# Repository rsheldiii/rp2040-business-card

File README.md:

# How to make Doom run on a business card!

Maybe you're like me, you're mindlessly scrolling through social media and between all the NileRed and LegalEagle shorts you see a video about someone running Doom on their smart fridge or something. You LQTM and keep scrolling, but something's nagging at the back of your brain — why Doom? ow do people even figure this stuff out? And, can I do something like that? I'm here to tell you you can, even if - like me - you don't have a single hardware hacker bone in your body.

# What is Doom? What is "It Runs Doom"?

Let's do some quick housekeeping, just in case:

## What is Doom?

Doom is a popular 1990's shooter game - a boomer shooter, but back when boomer shooters were just called shooters, but also... did Boomers play shooters? Doom came out in 1993, boomers were like 40 years old by then. Anyways, Doom builds off the fundamentals of predecessors like Wolfenstein, featuring a first-person perspective, an arsenal of weaponry and intricate level design. Doom's code was famously open-sourced, and famously well written, which has, in part, led to the proliferation of the "It Runs Doom" meme. If you'd like to learn more about how Doom works, I highly recommend the ["Game Engine Black Book Doom"](https://fabiensanglard.net/gebbdoom/), which goes into much more detail than I would be able to.

## What is "It Runs Doom"?

"It Runs Doom" is a popular [memetic construct](https://knowyourmeme.com/memes/it-runs-doom) where by pure skill or psychotic devotion, a programmer gets Doom running on something it probably shouldn't. Maybe that's a printer, or an ipod mini, or an oscilloscope, or even... a pregnancy test? Well, yes, but also... no. but... kind of?

# What qualifies as "Running Doom"?

I'd argue there are 3 main ways to run Doom on something: 

## Compilation 

The first, and most classic, is via compilation: you upload a program to the device that uses the device's original hardware to interpret and display Doom. Depending on the device, this is easier or harder than you might think; if the device is using a common, powerful consumer chip and has an exposed UART or other debug programming header, it could be about as easy as writing a screen driver. If the device is locked down, or Doom hasn't ever been compiled for the hardware, or you hit memory or space limitations, things can spiral in complexity pretty quickly. At the end of the day though, making Doom run on original hardware breaks down into three high-level steps:

1. You need to gain write access
2. You need to compile doom for the hardware target, taking into account any hardware limitations
3. You need to adapt the display, audio, and input code to use the device's hardware

That's about as much as I'm qualified to explain due to aforementioned lack of hardware-hacking ossicles. There are thousands upon thousands of different types of consumer devices with the capability to run Doom, and probably just as many people better equipped to explain how to do so, so we'll leave this category to the side for now.

# Display

The second way to run Doom applies to things like dot matrix displays or an oscilloscope: you get Doom running on something _else_ in a way that the display device can interpret. The name of the game here is to find a device that can both play Doom and talk to the display in whatever way the display wants to be talked to, then do both at the same time. That can be very straightforward in the case of a dot matrix display, but can get _very_ complicated - like when running doom on a [stock NES](https://youtu.be/FzVN9kIUNxw). This is not a port, somebody stuck an entire raspberry pi in a NES cartridge and made it spit out code that "tricks" the NES into displaying Doom, which is absolutely insane.

# Creation

The final way to run Doom is to take the original hardware _out_ of the device and run Doom on custom-built hardware _inside_ the device, the most famous example of this being the [pregnancy test](https://www.popularmechanics.com/science/a33957256/this-programmer-figured-out-how-to-play-doom-on-a-pregnancy-test/), but I also made a [keycap](https://github.com/rsheldiii/rp2040-doom-lcd) that runs doom, and [this madlad](https://youtu.be/o76U0JPrMFk) got Doom running on a LEGO brick in much the same way. 

While this is not nearly the same as hacking Doom onto a printer while sidestepping encryption and sniffing protocols, it's not the soulless copout some people would have you believe. If you make your own device that runs Doom, you'll gain a ton of knowledge about:

* PCB design
* Crystal oscillator circuits
* The USB specification
* Miniaturization and efficient trace routing
* Early 90's programming
* And more! 

I'm going to walk you through everything I learned getting Doom to run in a couple of different form factors so that you too can make your own device that runs Doom!

# Creating a PCB that runs Doom

The best way to solve a difficult problem is to remove constraints until you can solve it, then add them back one by one. _Understanding_ a problem mirrors this construction; Using my keycap to demonstrate how to design a device that can run Doom would be confusing, as I was designing for a small form factor. Components are crushed together, vias are placed in the middle of pads, traces take 90-degree turns where they really shouldn't take 90-degree turns, the works. I don't want you picking up any more of my bad habits than absolutely necessary, so let's start with something a bit more straightforward, and a LOT bigger: My business card!

I want to stress this is not _the_ business card that runs doom, it is _a_ business card that _can_ run doom. it can also run a NES emulator and lots of other things too, and has a handy set of GPIO pins at the top. Despite the larger form factor, the circuit is fundamentally the same, just all on one side and much easier to follow.

# Prototyping

But, how did we get here? How did we go from saying "I want to run Doom on my X" to having an X that runs Doom?

Well, step 0 is to have somebody else do it first. Graham Sanderson from the Raspberry Pi foundation wrote a _fantastic_ port of Choco Doom as part of the promotional material for the RP2040. Graham jumped through an amazing amount of hoops to get Doom running on the RP2040, like optimizing WAD file size by over 50% and writing some assembler PIO code to output to VGA, which can be displayed via HDMI. I took Graham's code and built off of it by uh... very carefully ripping out some of those optimizations, and implementing some generic SPI/I2c screen support. if you'd like to learn more about the crazy stuff graham did in his port, I highly recommend his detailed rundown on his [github page](https://kilograham.github.io/rp2040-doom/).

So after step 0, step 1 is to prototype. This mess of wires:

is my original prototype, and believe it or not, it still works! Prototyping is all about the loop: 

* Get to a known good state, then
* Implement a new feature (and inevitably break the build)

then repeat. For this project, that meant flashing the firmware in the first place, then getting just the LED blinking every frame, then unwinding the DVI linebuffer code in favor of a generic SPI / I2c interface. The actual process for this step is very boring, and I've already done it for you, so we'll move on from here.

So now we've got our prototype working, Doom is playing on a Raspberry Pi Pico hooked up to an Adafruit amplifier board (more on that later) and an OLED breakout. I could have made a carrier board for all these devices, slapped my name and email on it and called it a day; that's definitely a business card, and it would definitely run Doom. But we'd be wasting a lot of the potential of the pico with it's 26 I/O pins, it'd be impossible to make small enough to fit in a keycap, and also that's pretty underwhelming.

So, If we wanted to make our own, custom board, what would it need to "run" Doom? like, what components from the ones we've already assembled are necessary for that purpose?

# Component Requirements

### Processor

For starters, you need a processor, and we've got ourselves covered with the Raspberry Pi RP2040. Featuring a dual-core Arm Cortex m0, 264KB of SRAM, and support for up to 16MB of flash... it doesn't seem like it's big enough, does it? I mean, it's way fast enough, but I'll be forever in awe of how Graham got doom running on a 16th of the original RAM requirements. We could use the new RP2350 here - in fact Doom would run even better - but I'll be damned if I can find the bare MCU anywhere...

### Crystal Oscillator

but what else do you need to run Doom? Well, the RP2040 _needs_ a crystal oscillator... sort of. Every microcontroller needs at least one oscillator to run the clock, but the RP2040 already has an oscillator, it just kind of sucks. it's there for boot initialization, but it's accuracy is terrible, literally between 1.8 and 12MHZ. You can physically run the RP2040 without an external crystal, and the rp2040 might crunch the numbers that could theoretically put Doom on a screen, but you'd have to clock an i2c screen way, _way_ down to get anything to show - we're talking a couple FPS at most. So in any case, in our circumstance, we absolutely need an external crystal oscillator.

### Flash

You also need a flash chip, so you can store Doom. Think of flash as the hard drive of the microcontroller. When compiled for the rp2040, the game code itself is only about half a megabyte, but remember how I said Doom was open-source? well, Doom the _engine_ is open source, but doom the _game_ is not, and clocks in at around 11 megabytes. Graham's compression algorithm cuts that in more than half if you remember, so you're fine with 8 megs of flash. The rp2040 is kind of particular about flash chips? we'll get to that later.

### Power

You'll need power as well, obviously. If you're not worried about efficiency, power can be pretty simple; we're going to use an LDO, or low drop-out voltage regulator, to get the RP2040 the 3.3 volts it needs from the USB lines. You could use a buck converter for higher efficiency but they usually require more support components, so we'll stick with the LDO for now.

### Is that it?

Now, some very select people might argue that you could stop here. You power the system, the microcontroller uses the crystal to communicate at high speeds with the flash chip, pulling the information it needs to run Doom - it just... doesn't display it anywhere. A younger me would argue this is sufficient - if I unplug my monitor, does my computer stop running? When I unplug the screen from my business card, each flash of the LED is another frame rendered into the ether. Is it not "running" Doom? 

But that's not really what we mean when something "plays" doom. Video games are multi-sensory, interactive experiences, if you can't _play_ a game, is it really a game at all? To that end, we need three more things: we need a screen, we need some way to input commands, and we need audio.

### Screen

Now, there are _hundreds_ of ways to add a screen to a raspberry pi. The proliferation of smart devices has ensured that aliexpress and its ilk are absolutely ensconced in a crusty layer of mini TFT and OLED screens. I found a couple SPI screens that use the same ribbon cable, meaning I can run either of them with a single footprint, but if you're willing to implement a screen driver you can use whatever you want - provided you can drive it fast enough. Whatever screen you get, make sure there's at least a good data sheet on the screen controller, or even better, a screen driver already implemented somewhere.

### Audio

For audio, I'm using an i2s amplifier. Why i2s you ask? That's uh... that's what Graham was using. The amp I'm using is in the same family as the Max98357 audio amplifier. Why _that_ audio amplifier you ask? Adafruit had a nice circuit diagram for it! In all seriousness though, the audio was already implemented, and there's a very popular, very standard amplifier that works great, so why change things? Just take the win.

### Input

Speaking of wins, for input I'm sticking with the USB input that's already implemented. You could certainly add a set of buttons that trigger of GPIO pins with some interrupts that set a bitmask that you key in to blah blah blah. Or, you could just use the USB communication that's _already implemented_, and let people use a nice, full-size keyboard for control input - or a trackball, like [this guy did](https://github.com/arkadijs/rp2040-doom/tree/rp2040-mipi)

# How was I supposed to know all that?

So that covers all the components needed to run Doom, but you might be asking, how was I supposed to know I needed all these things in the first place? Like, a 12mhz crystal oscillator? what? 

Let me introduce you, my friends, to the [RP2040 datasheet](https://datasheets.raspberrypi.com/rp2040/rp2040-datasheet.pdf). Calling it a datasheet is a bit of a misnomer: this thing is a tome. I'm pretty sure if you read this thing front to back you become a technomancer. The rp2040 datasheet is chock full of fantastic information about how the RP2040 runs and how to interact with the chip once you've got it up and running. It's where I learned about the internal oscillator, the UART debug mode, and very importantly, the [_minimal design example_](https://datasheets.raspberrypi.com/rp2040/Minimal-KiCAD.zip):

The _minimal design example_ is a reference implementation of an RP2040-based microcontroller. It's not the best microcontroller out there - it doesn't even have a status LED - but it's the bare minimum components required to get the RP2040 running stably. 

If you take a look at the pcb, you'll notice the crystal oscillator circuit looks fairly similar to the circuit on my board as well - that's because I just straight up copy-pasted it into my design before modifying it slightly. That might feel like a cop-out, but hardware manufactures, really, _really_ want you to use reference designs. They spend significant amounts of time and effort designing their chips and testing the physical and electrical properties of their devices, they'd _really_ prefer you just stick to the reference designs so the chip works just as it should. Fun little side note, the Raspberry Pi foundation actually [got burnt](https://arstechnica.com/gadgets/2019/07/raspberry-pi-4-uses-incorrect-usb-c-design-wont-work-with-some-chargers/) by not following reference designs in the past with one of their USB-C chargers, so even large companies are fallible to design mistakes.

# Introducing Kicad

OK, so we've got a reference design to base our PCB off of and the list of parts we're going to use, but how do we actually _use_ the reference design to design our PCB? Well, the reference design is a Kicad project, which happens to be a free PCB design software! Learning how to use kicad is it's own topic, and I'm not very qualified to teach it, but I learned by watching the "Getting To Blinky" series by [Contextual Electronics](https://www.youtube.com/watch?v=BVhWh3AsXQs&list=PLy2022BX6EspFAKBCgRuEuzapuz_4aJCn). Those tutorials have not been updated since Kicad 5, but there really hasn't been that much groundbreaking stuff between 5 and 7, so they're still a good watch. 

A nice thing about Kicad is the circuit and schematic designs are separate - you can lay out a circuit that performs a particular function, then link circuit symbols to schematic footprints. Once you switch to the PCB editor, those schematic footprints are linked together with what's called the "rat's nest", which correctly link together the pins of the components you laid out in the circuit diagram. neat!

Now that we have our EDA and a couple reference designs to base our components off of, we'll use the designs and the datasheets for the components to create a circuit for our custom board.

# The Circuit

While we're here, let's quickly go over some parts of the schematic that might be confusing. I'm **absolutely** not an electrical engineer, I just cosplay as one on the weekends, so take my advice with a grain of salt, but hey, the thing works so...

## Power

Up in the top you'll see the power circuitry. This stuff is dead simple and mostly borrowed from the reference schematic. One thing to call out here are the resistors - these are required for the USB-C spec, and you need _both_ of them so the plug can orient itself. Could you use one resistor and have the device still work? Probably, but I'm not in the business of probablies, go talk to the horseshoe company or whatever.

## Crystal Oscillator

Down below power delivery is the crystal oscillator. My advice is to use the reference crystal and just _never touch this part of the circuit again_. Crystal oscillators are effectively black magic, they are crazy susceptible to noise and other issues, if you get it working just leave it alone. It's actually so common to have a crystal that needs extra time to stabilize that there's a build variable - PICO_XOSC_STARTUP_DELAY_MULTIPLIER - that does so. If the reference crystal is out of stock try to find the most comparable crystal, follow the datasheet's recommendations for resistance and capacitance, stitch a healthy ground plane away from high-speed signals, enable the build variable and cross your fingers.

## Flash

After the crystal is the flash circuitry, which is ripped right out of the reference schematic. I would highly recommend staying within the same family of Winbond flash chips when you design your circuit, as the rp2040 is a bit picky about what chips it will talk with; I know the people over at [Digi-key's youtube channel](https://youtu.be/kcwvuwetgEQ?t=2979) had some trouble in this department, though that is still an excellent video to watch if you want a more general look at hardware development for the RP2040. 

## Audio

Looping around, we have the amplifier circuitry. This is very similar to Adafruit's Max98357 schematic. All resistor values were determined by looking at the data sheet to give us 9db of gain and a 50/50 mono output. It's worth noting that the Max98357 is a speaker amplifier, not a headphone amplifier; it might work with some really dinky headphones, but if you wanted a headphone-based system, you should be looking at a headphone amplifier instead.

## Screen

Making our way up here, we finally get to the screen. Schematically there isn't much to talk about here - like most small screens, the screens I'm using have their own drive circuitry, so we're really just connecting pins to bare pins here. Swapping to a new screen would require reviewing the screen's datasheet and rejiggering the connections here. The RP2040 is pretty unique in that the I2c and SPI pins can be one of many sets of pins across the board, so you can be pretty flexible with where you place the screen when designing the PCB.

## USB

Down at the bottom, we find ourselves at the USB hookup. The 27 ohm resistors (not shown) are required by the USB spec, the 56k resistors are the opposite of the resistors on the power usb - they indicate to the devices connected to the bus that we are an upstream-facing-port, and peripherals can expect power from us, since we need to power the keyboard. 

## Decoupling caps

Finally to round us off here, we find all these capacitors up at the top. These are decoupling capacitors, which are capacitors placed next to integrated circuits to absorb weird voltage spikes and dips, decoupling them from other stuff that's going on in the board. these decoupling caps are to be placed next to _every_ 3v3 pin on the rp2040. Lastly we have this LED hooked up to GPIO25 as a status LED, which is _very_ helpful if you can't get a debug session working.

# The PCB

So now we've got the entire schematic laid out, and all we have to do is turn that into a PCB! In Kicad this happens in a two-step process: first, you agonizingly collect all the footprints for your selected components, scrutinizing and painstakingly fixing any mistakes made by the conversion program that spit them out, and then you lay them all out in PCBNew and connect everything up! When I say agonizingly, I do mean _agonizingly_; I have not figured out a good way to do this. There are dozens of sites that claim to be a one-stop shop for all your eda footprint needs, but every one I've tried suffers from some sort of problem. Whether it's something mundane like terrible inventory, to something more systemic like whatever the heck Mouser's got going on, they all have their faults. For now I've settled on UltraLibrarian, which has a good set of footprints, and sometimes even 3d models, but the pins don't always make sense.

Once you have all your footprints downloaded, imported, and associated, you can start designing your PCB:

The blue lines are the "rat's nest" we talked about earlier. Your job is to eliminate all of these blue lines while following common PCB design rules and the constraints put on you by the fab. Then you run the design rules checker and do whatever it says - within reason. It's almost a game really, and real EEs are _much_ better at it than I am. But, this is what I came up with:

Power is in the top left, with audio at the bottom left, input at the bottom, flash at the bottom right, the screen top right, and finally the crystal oscillator (and GPIO) at the top. You can see that the USB lines are straight and impedance matched, we've got a nice, stitched ground plane under the crystal oscillator and the trace runs for most components are pretty short. I can already see one sin I committed, I put the 27ohm resistors for the USB lines at the USB connector, when they should be closer to the RP2040. However, "Closer" is a relative term, and we're super over-engineering this dinky lil USB bus here, so we'll be perfectly fine. That goes for the impedance and length matching as well.

# Fabrication

Now we've got a PCB that runs Doom in theory, but how do we get a PCB that runs doom... in practice?

well, you send your design to a fab! Each fab has their own rules and constraints listed on their website, sometimes with step-by-step tutorials on how to configure your EDA for their service; it's a good idea to run through these and make sure your board complies. Shoutouts to [OSHPark](https://www.oshpark.com) here who are a pretty phenomenal, US-based fab. I use them for prototyping as they don't have a minimum price. Plus, you can upload your Kicad project directly to them instead of having to generate gerber files! You have to buy stencils on a separate website but they are reasonably priced and even have a neat lil' import button. You're gonna _need_ stencils by the way, unless you can hand-solder a QFN56.

# Assembly

Once you've got your boards back from the fab, it's time for assembly. Since we built our boards around an rp2040, that means we basically have to do reflow soldering, which involves using a stencil to spread solder paste onto a pcb, placing components on the solder blobs and then "reflowing" that solder to stick the parts on the board. 

There are some tricks you can do to make this easier. Remember when I said my business card has all the components on the same side? That means I can use this little hot plate:

 to reflow 100% of the components with a single stencil. You can also use as many hand-solderable components as you can get your hands on, keeping all the non-hand-solderable components on the same side of the board. This again lets you only reflow with a single stencil, just with a little extra soldering afterwards.

I gotta be honest, even with these tricks I'm not great at this. It's best to get the solder all in one smooth motion but I always need to come back and do another go-round. Luckily you can still do some manual fixup if your solder job is uh... less than ideal.

Counter-intuitively, I find that power is everything when you're doing fixup drag-soldering like this. The more amps your soldering iron can push out, the better. My Hakko FX888D is a little beefier than my Pinecil and that makes all the difference in how easy it is to fix solder bridges. Also be sure to select a tip that can actually get into the space between the PCB and the component!

# Flashing / Programming

OK, you're now the proud owner of a custom-built PCB. Nobody else in the _world_ has a device like this in their hands, which can be kind of daunting. Like, forget Doom, how do I even get _any_ program on this device?

Luckily that's pretty easy, you boot the sucker up and press the boot button and wham bam thank you mam, bob's your uncle bessie's your aunt, you've got a USB mass storage device you can _copy_ your program onto! I cannot tell you how much of a mind-blown moment I had the first time I plugged in a Raspberry Pi Pico and saw this. This USB firmware is _embedded into the board_, it's basically impossible to brick. It's amazing. I'm so sick of programming headers and weird little boot rituals and all that junk, I want every microcontroller to use this bootloader.

The first program you should chuck on your PCB is the led blink example from the rp2040 datasheet, but that's boring, so we're going to head on over to the rp2040-doom-lcd github page and download us some Doom firmware. If you don't have your own PCB that's ok, there are a couple off-the-shelf boards that are supported as well, like the [Lilygo TT-Go T-display](https://www.aliexpress.us/item/3256803094729227.html), or these tiny little unnamed [0.42 inch RP2040 boards](https://www.aliexpress.us/item/3256805864747243.html). If you find another board that uses one of the [supported screens](https://github.com/rsheldiii/rp2040-doom-LCD/tree/rp2040/src/pico/pico-screens/screens), it should be relatively simple to get it up and running as well.

So you download your uf2 file, put your PCB into boot mode, chuck that sucker in the folder aaaand... nothing? well, _almost_ nothing. you should see the LED flash just a tiny bit when you plug things in, which probably indicates that you forgot to place the level code in memory. For testing purposes you can download the shareware version of doom free of charge. to grab the full game file, the easiest way is to pay for it on Steam; the 1-800 number the shareware file gives you is out of order, unfortunately. Once you've followed the instructions about how to shrink and load the level file into memory using picotool, _now_ you're ready for the moment of truth. 

And that's it, you got Doom playing on a custom PCB! It can be a little finnicky with what keyboards it'll allow to be connected to it, but once you do you have full control over the game. My spi / i2c code does not use DMA, but I haven't found any framerate issues; if you're implementing a larger display and having some trouble, that would be a good place to start. 

# What's next?

So where do we go from here? Well, a million different places, honestly. You could add a bluetooth chip and play with a game controller, or make the first electric gloves that run Doom, make a GPIO add-on for the flipper zero, or any number of different things. You'll need a PCB to use / modify though; unless you were following along, that's probably not in your possession right now. I don't want you to start from scratch, but I also don't want to just give out the files for my business card since it would be trivial to delete my name and slap someone elses in there. I'll do you one better by releasing this board:

I'm calling it the Doom Stamp. It's got:

* The same circuit as my business card in a very compact form factor (Status LED, separate power / data USB, boot button, optional power diodes, etc etc)
* 2-layer, 1-sided board for easy fabrication
* M2 mounting holes 
* A nice screw terminal for connecting external speakers

The Kicad files are available in [this repository](https://github.com/rsheldiii/rp2040-business-card) in the DoomStamp directory. Note that while the schematic is functionally identical and all components (save the speaker) remain the same, this exact pcb has *NOT BEEN TESTED* yet; I have boards on the way.

If you just want to play around with a tiny board built to run Doom, feel free to send the Kicad pcb file off to OSHPark (3 boards are ~$10) or generate your own gerbers. If you want to use my design as a starting point for your own creation, by all means!

# BOM shenanigans

You can generate the BOM in the schematic editor; there are also pre-generated BOMs at the base of the Kicad project. A few things to note:

### Crystal

The crystal is **NOT** the reference crystal, as they were out of stock when I made the original circuit. The crystal I used is [this one](https://www.mouser.com/ProductDetail/774-403C35E12M00000), though case-compatible 12mhz crystals will work in the circuit as long as you tweak the support capacitors.

### MCU

It's weirdly difficult to find RP2040 MCUs on Mouser, but they are [here](https://www.mouser.com/ProductDetail/358-SC091413)

### Flash

use the flash specified in the RP2040 datasheet

### Audio

find whichever Max9835x is in stock and double check via the datasheet that it's a drop-in replacement for the Max98357.

For the speaker terminal, the BOM csv has the part number (I haven't purchased it yet, so I don't have the link). You could also elect not to fill this component, and directly solder speaker wires, either way.

### Voltage Regulator

the voltage regulator I used was [this one](https://www.mouser.com/ProductDetail/onsemi/NCV1117ST33T3G?qs=8sOby8ZxZLHgqg5CFzeqiA%3D%3D), but I'd certainly look for comparable LDOs that are cheaper

### Screen / Screen FPC

the screen FPC I used is [this one](https://www.mouser.com/ProductDetail/TE-Connectivity/2328702-8?qs=w/v1CP2dgqphyFkupQxKkA%3D%3D). This FPC interfaces with two SPI displays that I know about. I purchased them from [this link](https://www.aliexpress.us/item/3256803794221438.html?gatewayAdapt=glo2usa), the 0.96 and the 1.14 inch version (the 1.14 being showcased in this document, as it is bigger and has much better colors). There may be other screens that work, though the code will need to be modified. 

### Boot Switch

the component photo is of a white switch, but the boot switch is [this one](https://www.mouser.com/ProductDetail/611-PTS636SL50SMTRLF)

### USBs

the two USB components used are [here](https://www.mouser.com/ProductDetail/640-USB4135-GF-A) and [here](https://www.mouser.com/ProductDetail/640-USB4105-GF-A-060)

### USB Diodes

the USB diodes are DNF; they would theoretically provide protection for the USB circuit and enforce power direction, but they're a little difficult to come by at the power I chose for the LDO. You'll need to bridge these pads, either with a wire, a 0-ohm resistor that's compatible with the footprint, or just solder. You could also use a regulator with less capacity and thus easier-to-find supporting diodes. Note that with the diodes installed, you need to provide separate power when programming the device, as the bottom usb will only be used for communication. 

# Does it _really_ play Doom though?

Indeed, so far throughout this document, I haven't provided any proof that the business card actually works. For posterity, I play the first level of Doom on the business card [here](https://youtu.be/YhjtOR5cU4k). Is that enough proof? what if I'm beaming a video of Doom via the USB port? I guess that means to _really_ prove it, you'll have to assemble a Doom Stamp and try it out for yourself.

# That's it

That's all, thanks for reading!

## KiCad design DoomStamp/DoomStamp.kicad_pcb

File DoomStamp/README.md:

The Doom Stamp was based off the RP2040 [Minimal Design Example](https://datasheets.raspberrypi.com/rp2040/Minimal-KiCAD.zip), and is designed as a platform to make embedded devices that run Doom (or indeed, embedded devices with i2s audio and SPI displays).

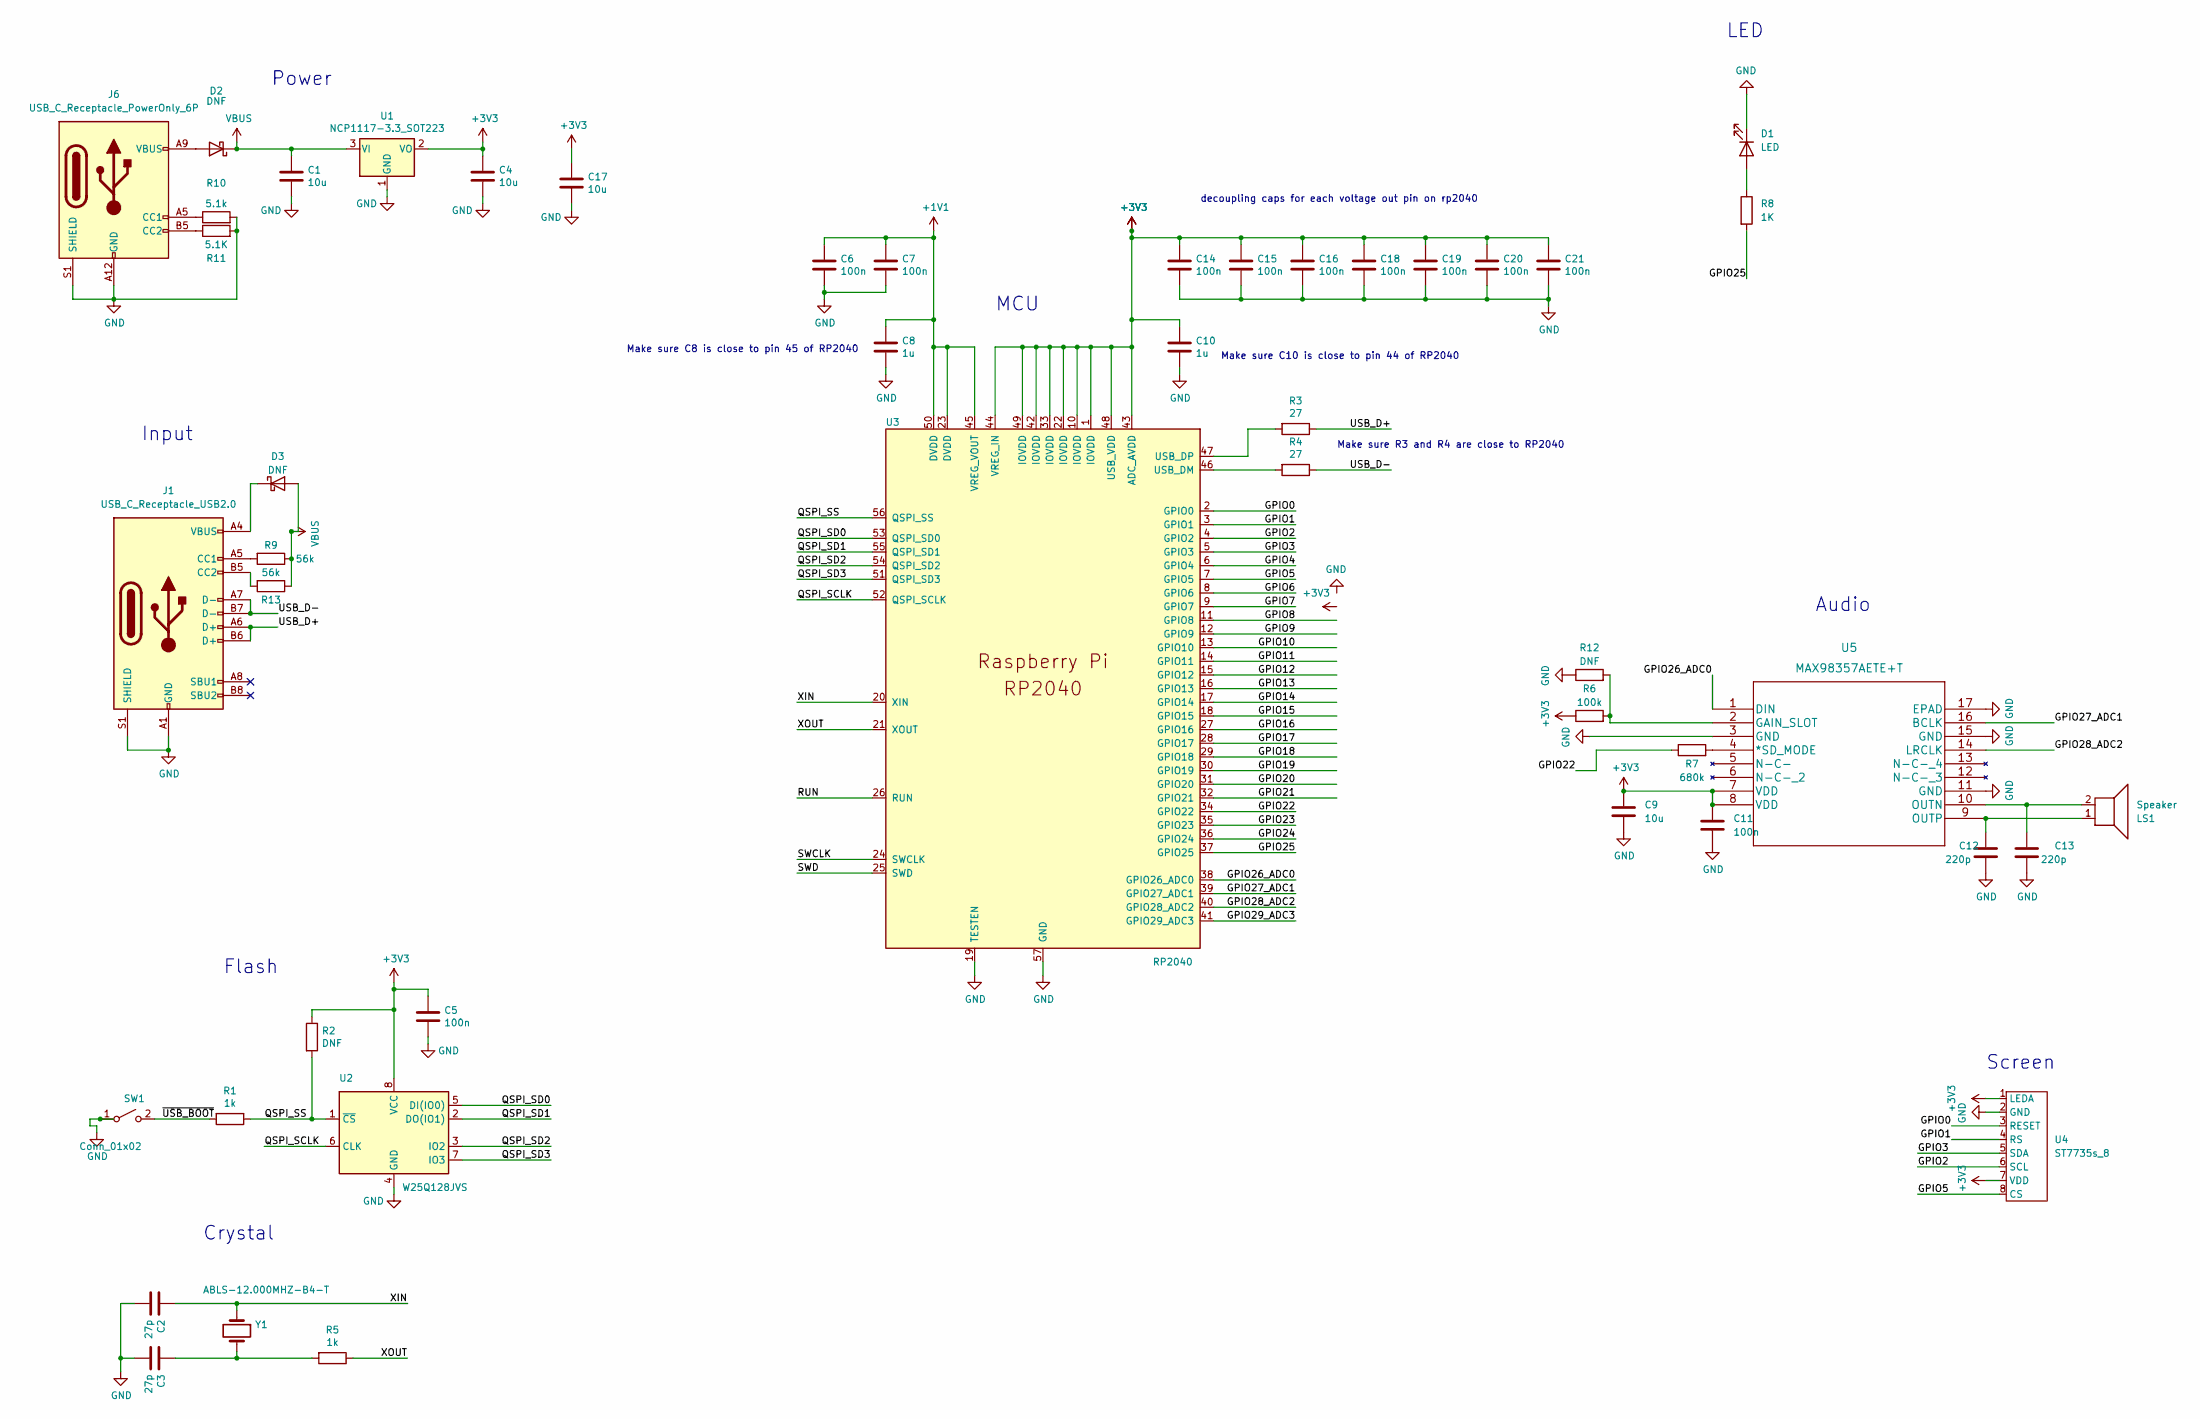
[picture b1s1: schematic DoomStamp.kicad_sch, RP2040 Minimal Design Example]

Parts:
C1, C4, C9, C17: 10u; C_0402_1005Metric
C2, C3: 27p; C_0402_1005Metric
C5, C6, C7, C11, C14, C15, C16, C18, C19, C20, C21: 100n; C_0402_1005Metric
C8, C10: 1u; C_0402_1005Metric
C12, C13: 220p; C_0402_1005Metric
D1: LED; LED_0603_1608Metric
D2, D3: DNF; D_0805_2012Metric
J1: USB_C_Receptacle_USB2.0; GCT_USB4105-GF-A
J6: USB_C_Receptacle_PowerOnly_6P; USB_C_Receptacle_GCT_USB4135-GF-A_6P_TopMnt_Horizontal
LS1: Speaker; TerminalBlock_Phoenix_MPT-0,5-2-2.54_1x02_P2.54mm_Horizontal
R1, R5: 1k; R_0402_1005Metric
R2, R12: DNF; R_0402_1005Metric
R3, R4: 27; R_0402_1005Metric
R6: 100k; R_0402_1005Metric
R7: 680k; R_0402_1005Metric
R8: 1K; R_0402_1005Metric
R9, R13: 56k; R_0402_1005Metric
R10: 5.1k; R_0402_1005Metric
R11: 5.1K; R_0402_1005Metric
SW1: Conn_01x02; PTS636_SL50_SMTR_LFS Tactile Switch
U1: NCP1117-3.3_SOT223; SOT-223-3_TabPin2
U2: W25Q128JVS; SOIC-8_5.23x5.23mm_P1.27mm
U3: RP2040; RP2040-QFN-56
U4: ST7735s_8; 2328702-8 IPS screen FPC
U5: MAX98357AETE+T; MAX98357AETE-T
Y1: ABLS-12.000MHZ-B4-T; 403C35D12M00000

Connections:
+1V1: C6.1, C7.1, C8.1, U3.23 (DVDD), U3.45 (VREG_VOUT), U3.50 (DVDD)
+3V3: C4.1, C5.1, C9.1, C10.1, C11.1, C14.1, C15.1, C16.1, C17.1, C18.1, C19.1, C20.1, C21.1, R2.1, R6.1, U1.2 (VO), U2.8 (VCC), U3.1 (IOVDD), U3.10 (IOVDD), U3.22 (IOVDD), U3.33 (IOVDD), U3.42 (IOVDD), U3.43 (ADC_AVDD), U3.44 (VREG_IN), U3.48 (USB_VDD), U3.49 (IOVDD), U4.1 (LEDA), U4.7 (VDD), U5.7 (VDD), U5.8 (VDD)
/GPIO0: U3.2 (GPIO0), U4.3 (RESET)
/GPIO1: U3.3 (GPIO1), U4.4 (RS)
/GPIO2: U3.4 (GPIO2), U4.6 (SCL)
/GPIO3: U3.5 (GPIO3), U4.5 (SDA)
/GPIO4: U3.6 (GPIO4)
/GPIO5: U3.7 (GPIO5), U4.8 (CS)
/GPIO6: U3.8 (GPIO6)
/GPIO7: U3.9 (GPIO7)
/GPIO8: U3.11 (GPIO8)
/GPIO9: U3.12 (GPIO9)
/GPIO10: U3.13 (GPIO10)
/GPIO11: U3.14 (GPIO11)
/GPIO12: U3.15 (GPIO12)
/GPIO13: U3.16 (GPIO13)
/GPIO14: U3.17 (GPIO14)
/GPIO15: U3.18 (GPIO15)
/GPIO16: U3.27 (GPIO16)
/GPIO17: U3.28 (GPIO17)
/GPIO18: U3.29 (GPIO18)
/GPIO19: U3.30 (GPIO19)
/GPIO20: U3.31 (GPIO20)
/GPIO21: U3.32 (GPIO21)
/GPIO22: R7.1, U3.34 (GPIO22)
/GPIO23: U3.35 (GPIO23)
/GPIO24: U3.36 (GPIO24)
/GPIO25: R8.2, U3.37 (GPIO25)
/GPIO26_ADC0: U3.38 (GPIO26_ADC0), U5.1 (DIN)
/GPIO27_ADC1: U3.39 (GPIO27_ADC1), U5.16 (BCLK)
/GPIO28_ADC2: U3.40 (GPIO28_ADC2), U5.14 (LRCLK)
/GPIO29_ADC3: U3.41 (GPIO29_ADC3)
/QSPI_SCLK: U2.6 (CLK), U3.52 (QSPI_SCLK)
/QSPI_SD0: U2.5 (DI(IO0)), U3.53 (QSPI_SD0)
/QSPI_SD1: U2.2 (DO(IO1)), U3.55 (QSPI_SD1)
/QSPI_SD2: U2.3 (IO2), U3.54 (QSPI_SD2)
/QSPI_SD3: U2.7 (IO3), U3.51 (QSPI_SD3)
/QSPI_SS: R1.1, R2.2, U2.1 (~CS), U3.56 (QSPI_SS)
/RUN: U3.26 (RUN)
/SWCLK: U3.24 (SWCLK)
/SWD: U3.25 (SWD)
/USB_D+: J1.A6 (D+), J1.B6 (D+), R3.1
/USB_D-: J1.A7 (D-), J1.B7 (D-), R4.1
/XIN: C2.1, U3.20 (XIN), Y1.1
/XOUT: R5.1, U3.21 (XOUT)
/~USB_BOOT: R1.2, SW1.2 (B)
GND: C1.2, C2.2, C3.2, C4.2, C5.2, C6.2, C7.2, C8.2, C9.2, C10.2, C11.2, C12.2, C13.2, C14.2, C15.2, C16.2, C17.2, C18.2, C19.2, C20.2, C21.2, D1.1 (K), J1.A1 (GND), J1.A12 (GND), J1.B1 (GND), J1.B12 (GND), J1.S1 (SHIELD), J6.A12 (GND), J6.B12 (GND), J6.S1 (SHIELD), R10.2, R11.2, R12.1, SW1.1 (A), U1.1 (GND), U2.4 (GND), U3.19 (TESTEN), U3.57 (GND), U4.2 (GND), U5.3 (GND), U5.11 (GND), U5.15 (GND), U5.17 (EPAD)
unnamed: C3.1, R5.2, Y1.2
unnamed: D1.2 (A), R8.1
unnamed: D2.2 (A), J6.A9 (VBUS), J6.B9 (VBUS)
unnamed: D3.1 (K), J1.A4 (VBUS), J1.A9 (VBUS), J1.B4 (VBUS), J1.B9 (VBUS)
unnamed: J1.A5 (CC1), R9.2
unnamed: J1.B5 (CC2), R13.2
unnamed: J6.A5 (CC1), R10.1
unnamed: J6.B5 (CC2), R11.1
unnamed: R4.2, U3.46 (USB_DM)
unnamed: R3.2, U3.47 (USB_DP)
unnamed: R7.2, U5.4 (*SD_MODE)
unnamed: R6.2, R12.2, U5.2 (GAIN_SLOT)
unnamed: C13.1, LS1.2, U5.10 (OUTN)
unnamed: C12.1, LS1.1, U5.9 (OUTP)
VBUS: C1.1, D2.1 (K), D3.2 (A), R9.1, R13.1, U1.3 (VI)

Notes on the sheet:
Make sure C8 is close to pin 45 of RP2040
Make sure C10 is close to pin 44 of RP2040
Make sure R3 and R4 are close to RP2040
decoupling caps for each voltage out pin on rp2040
MCU
Screen
Flash
LED
Input
Crystal
Power
Audio

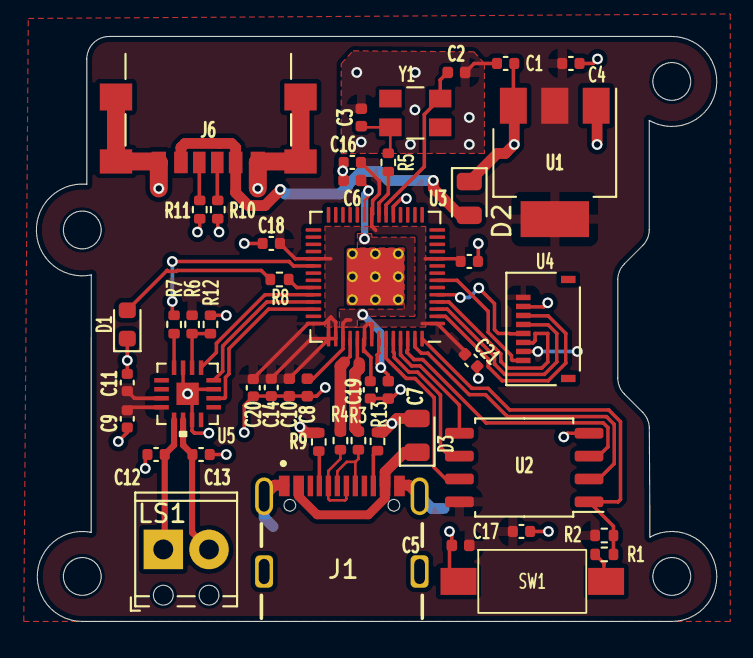
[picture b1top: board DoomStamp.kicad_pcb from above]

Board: 2 copper layers, 37.8 x 32.5 mm, 47 parts (0 on the bottom side), 38 nets.

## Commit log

2024-12-21 add 95% of everything
2024-12-24 add Doom stamp
2024-12-28 add mounting holes
    and some readme edits
2024-12-28 update mounting holes
2024-12-28 Add BOM
    and some README edits and schematic fixes
2024-12-28 add BOM explanation
    and DOOM STAMP on the doom stamp
2024-12-28 add link to Youtube video
2024-12-28 lots of spelling mistakes
    yeesh
2024-12-28 main
    main
2024-12-28 Title
    title
2024-12-28 add very short README for Doom Stamp
2024-12-28 add license
    as far as I understand, the RP2040 minimal design example is CC-BY-SA, and while my design is far removed from the example, it was based off the files initially, so let's go with this license
2024-12-28 attribution
2024-12-28 Doom Stamp -> DoomStamp

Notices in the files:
parts and their libraries:
Copyright 2021 Accelerated Designs. All rights reserved.
